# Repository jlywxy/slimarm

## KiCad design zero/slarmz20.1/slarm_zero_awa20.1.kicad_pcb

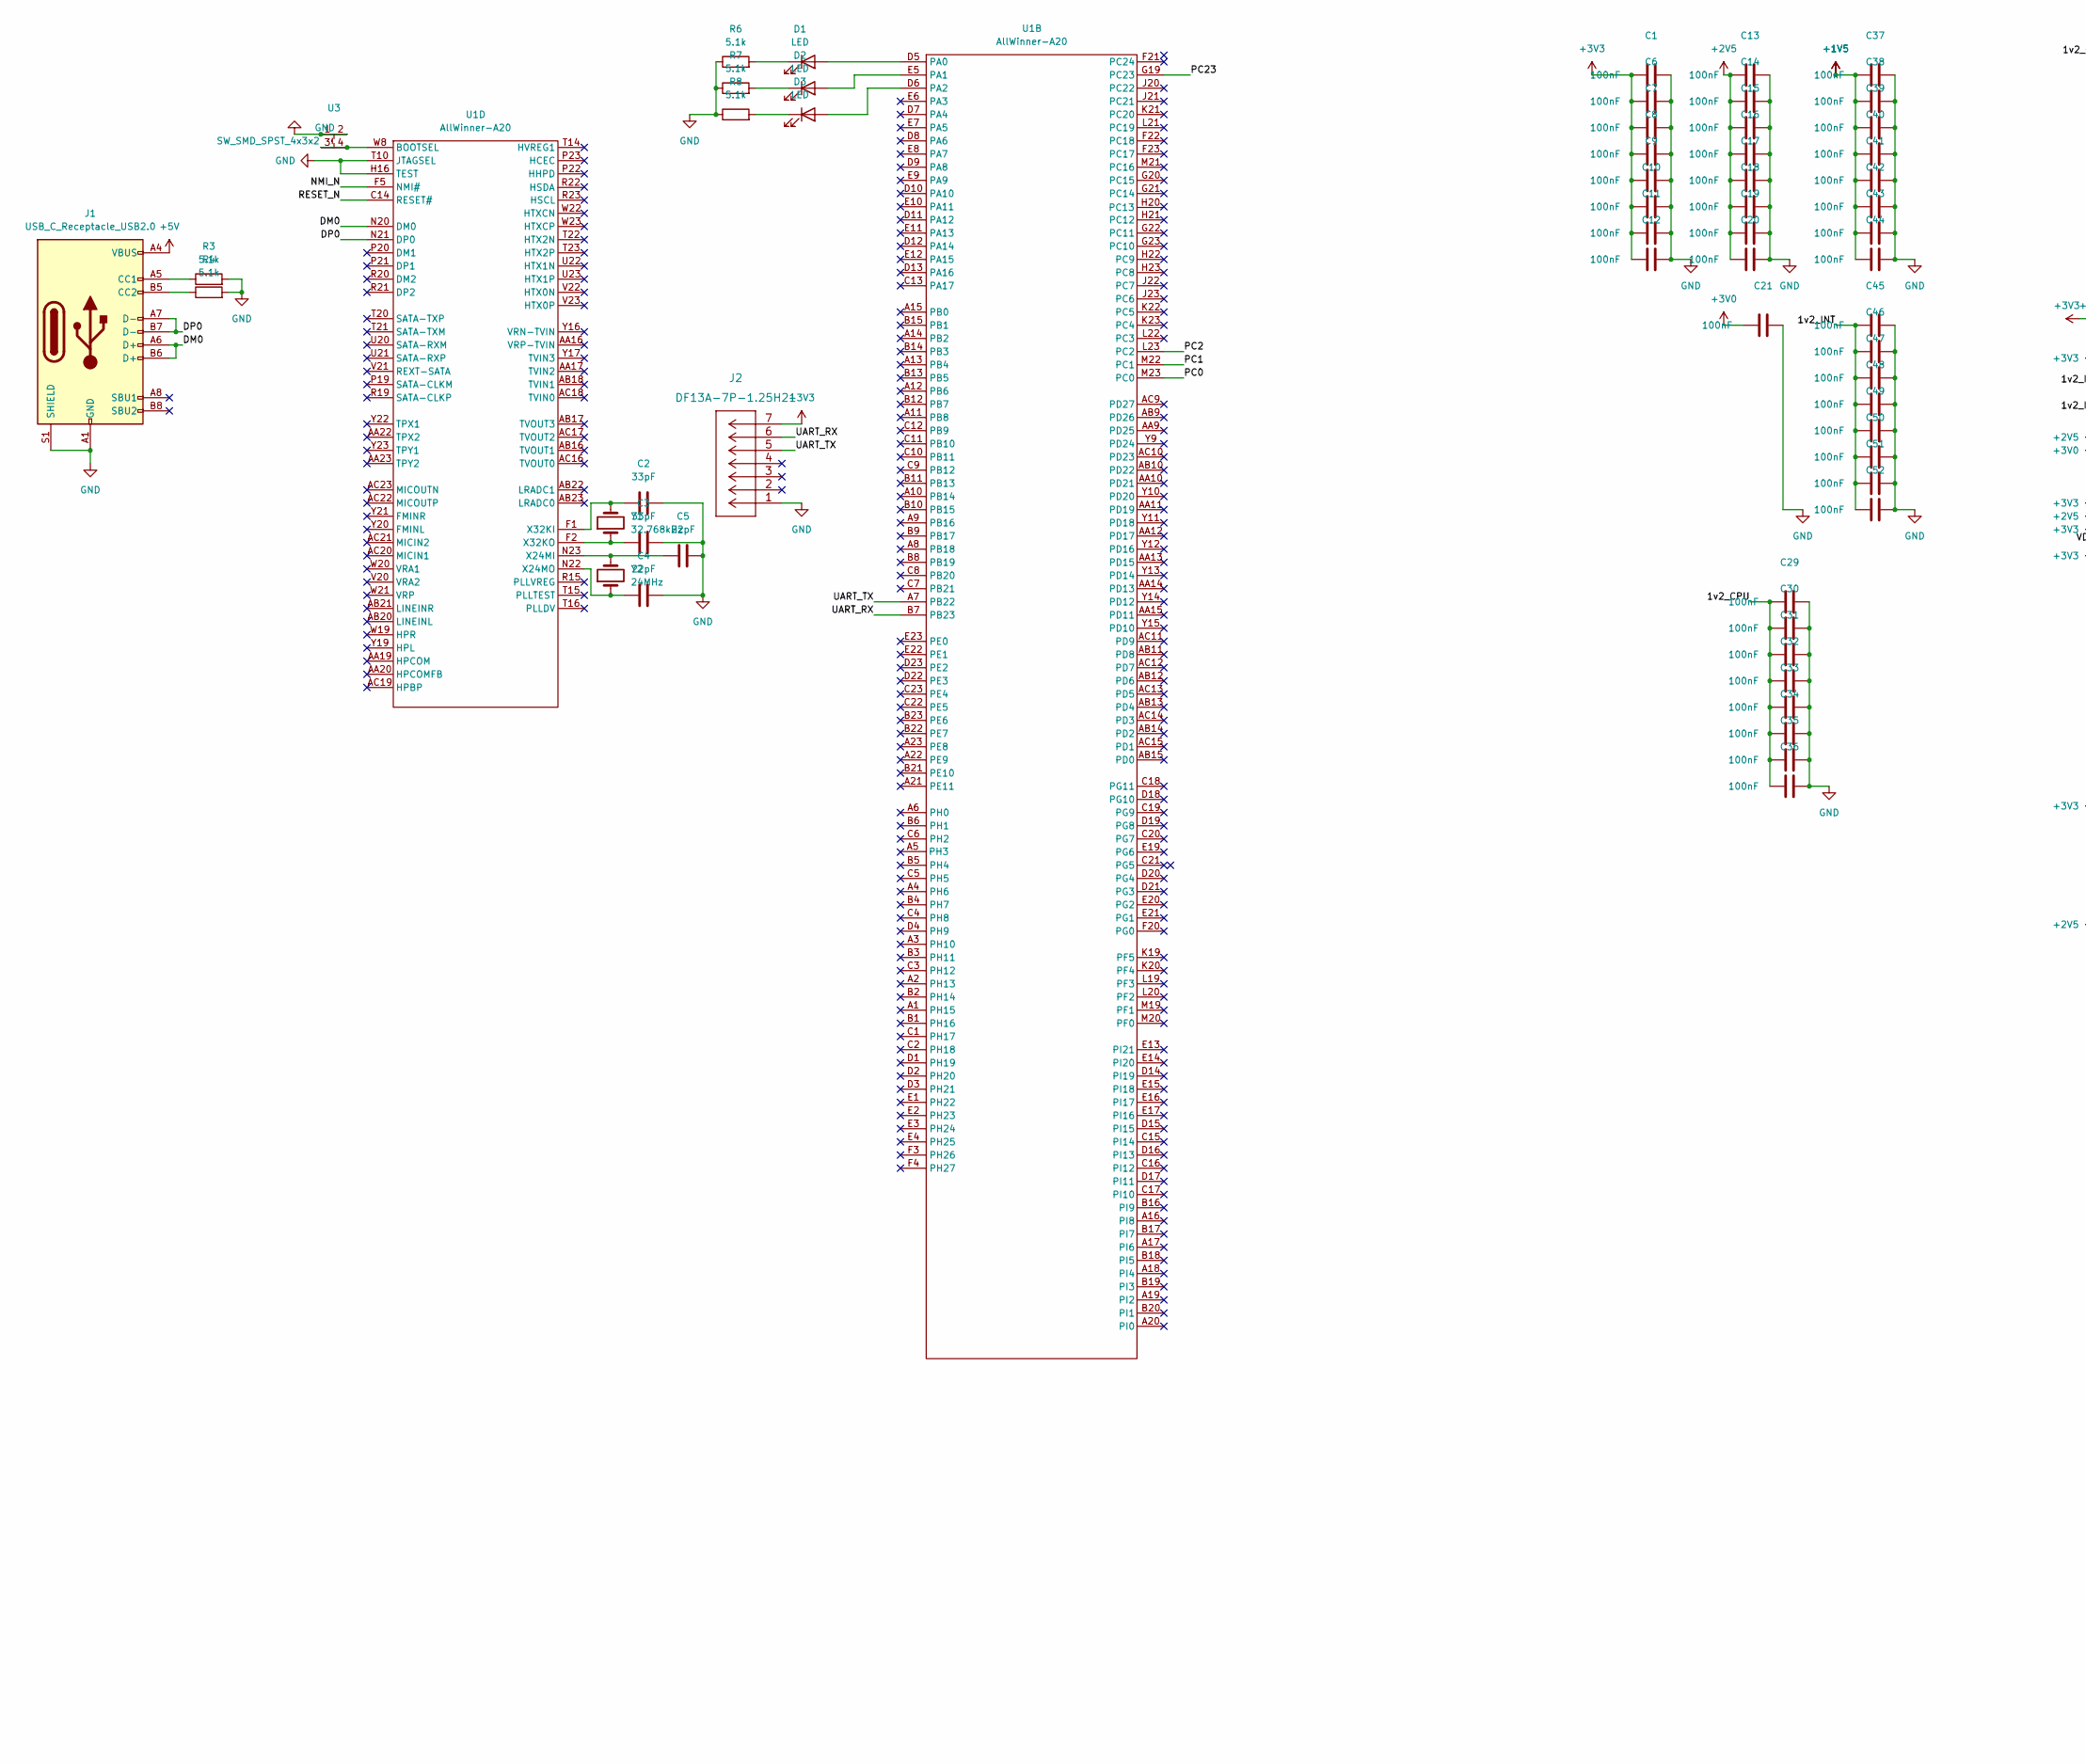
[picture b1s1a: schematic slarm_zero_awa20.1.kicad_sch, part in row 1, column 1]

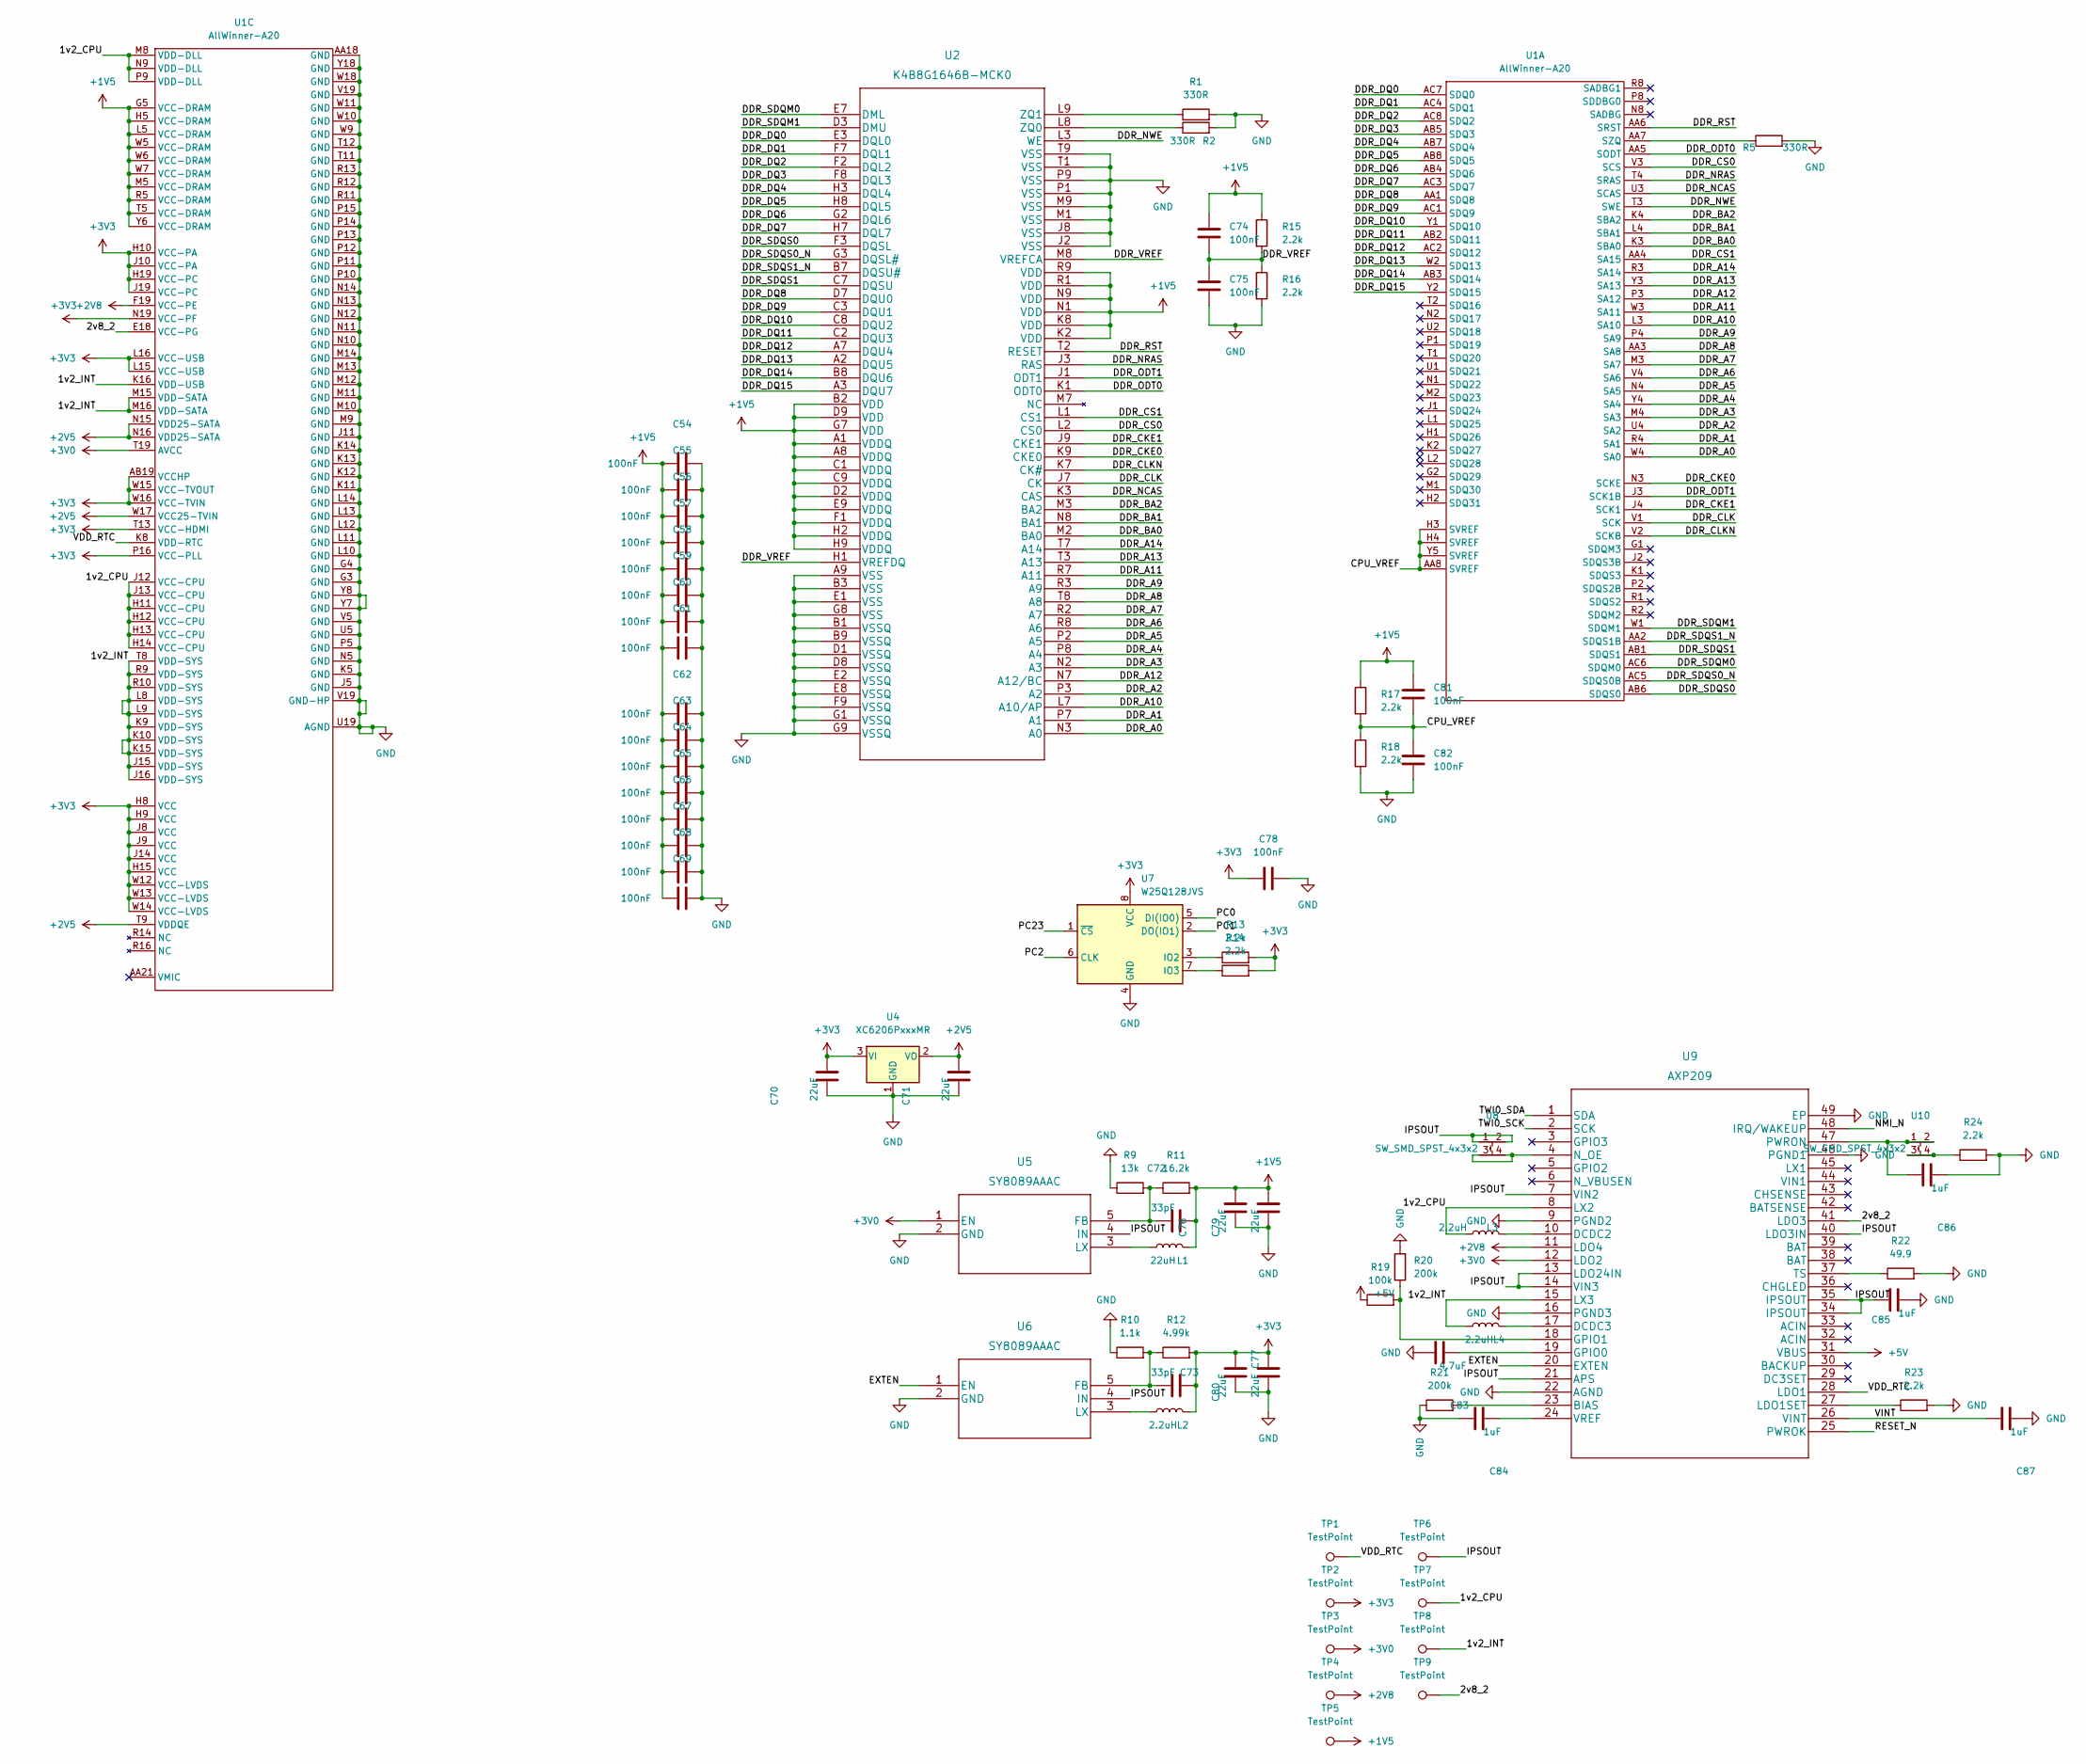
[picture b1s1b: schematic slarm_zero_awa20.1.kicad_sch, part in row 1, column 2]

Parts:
C1, C6, C7, C8, C9, C10, C11, C12, C13, C14, C15, C16, C17, C18, C19, C20, C21, C29, C30, C31, C32, C33, C34, C35, C36, C37, C38, C39, C40, C41, C42, C43, C44, C45, C46, C47, C48, C49, C50, C51, C52, C54, C55, C56, C57, C58, C59, C60, C61, C62, C63, C64, C65, C66, C67, C68, C69, C74, C75, C78, C81, C82: 100nF; C_0402_1005Metric
C2, C3: 33pF; C_0603_1608Metric
C4, C5: 22pF; C_0603_1608Metric
C70, C71, C76, C77, C79, C80: 22uF; C_0402_1005Metric
C72, C73: 33pF; C_0402_1005Metric
C83: 4.7uF; C_0402_1005Metric
C84, C85, C86, C87: 1uF; C_0402_1005Metric
D1, D2, D3: LED; LED_0603_1608Metric
J1: USB_C_Receptacle_USB2.0; USB_C_Receptacle_HRO_TYPE-C-31-M-12
J2: DF13A-7P-1.25H21
L1: 22uH; L_Vishay_IHLP-2525
L2, L3, L4: 2.2uH; L_Vishay_IHLP-2525
R1, R2, R5: 330R; R_0603_1608Metric
R3, R4, R6, R7, R8: 5.1k; R_0603_1608Metric
R9: 13k; R_0603_1608Metric
R10: 1.1k; R_0603_1608Metric
R11: 16.2k; R_0603_1608Metric
R12: 4.99k; R_0603_1608Metric
R13, R14, R15, R16, R17, R18, R23, R24: 2.2k; R_0603_1608Metric
R19: 100k; R_0603_1608Metric
R20, R21: 200k; R_0603_1608Metric
R22: 49.9; R_0603_1608Metric
TP1, TP2, TP3, TP4, TP5, TP6, TP7, TP8, TP9: TestPoint; TestPoint_Pad_D1.5mm
U1: AllWinner-A20; awa20
U2: K4B8G1646B-MCK0
U3, U8, U10: SW_SMD_SPST_4x3x2; SW_SPST_SWD_4x3x2
U4: XC6206PxxxMR; SOT-23-3
U5, U6: SY8089AAAC
U7: W25Q128JVS; SOIC-8_5.23x5.23mm_P1.27mm
U9: AXP209
Y1: 32.768kHz; Crystal_SMD_5032-2Pin_5.0x3.2mm
Y2: 24MHz; Crystal_SMD_5032-2Pin_5.0x3.2mm

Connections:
+1V5: C37.1, C38.1, C39.1, C40.1, C41.1, C42.1, C43.1, C44.1, C54.1, C55.1, C56.1, C57.1, C58.1, C59.1, C60.1, C61.1, C62.1, C63.1, C64.1, C65.1, C66.1, C67.1, C68.1, C69.1, C72.1, C74.2, C76.1, C79.1, C81.2, L1.2, R11.2, R15.1, R17.1, TP5.1, U1.G5 (VCC-DRAM), U1.H5 (VCC-DRAM), U1.L5 (VCC-DRAM), U1.M5 (VCC-DRAM), U1.R5 (VCC-DRAM), U1.T5 (VCC-DRAM), U1.W5 (VCC-DRAM), U1.W6 (VCC-DRAM), U1.W7 (VCC-DRAM), U1.Y6 (VCC-DRAM), U2.A1 (VDDQ), U2.A8 (VDDQ), U2.B2 (VDD), U2.C1 (VDDQ), U2.C9 (VDDQ), U2.D2 (VDDQ), U2.D9 (VDD), U2.E9 (VDDQ), U2.F1 (VDDQ), U2.G7 (VDD), U2.H2 (VDDQ), U2.H9 (VDDQ), U2.K2 (VDD), U2.K8 (VDD), U2.N1 (VDD), U2.N9 (VDD), U2.R1 (VDD), U2.R9 (VDD)
+2V5: C13.1, C14.1, C15.1, C16.1, C17.1, C18.1, C19.1, C20.1, C71.1, U1.N15 (VDD25-SATA), U1.N16 (VDD25-SATA), U1.T9 (VDDQE), U1.W17 (VCC25-TVIN), U4.2 (VO)
+2V8: TP4.1, U1.F19 (VCC-PE), U9.11 (LDO4)
+3V0: C21.1, TP3.1, U1.T19 (AVCC), U5.1 (EN), U9.12 (LDO2)
+3V3: C1.1, C6.1, C7.1, C8.1, C9.1, C10.1, C11.1, C12.1, C70.1, C73.1, C77.1, C78.1, C80.1, J2.7, L2.2, R12.2, R13.2, R14.2, TP2.1, U1.AB19 (VCCHP), U1.H8 (VCC), U1.H9 (VCC), U1.H10 (VCC-PA), U1.H15 (VCC), U1.H19 (VCC-PC), U1.J8 (VCC), U1.J9 (VCC), U1.J10 (VCC-PA), U1.J14 (VCC), U1.J19 (VCC-PC), U1.L15 (VCC-USB), U1.L16 (VCC-USB), U1.N19 (VCC-PF), U1.P16 (VCC-PLL), U1.T13 (VCC-HDMI), U1.W12 (VCC-LVDS), U1.W13 (VCC-LVDS), U1.W14 (VCC-LVDS), U1.W15 (VCC-TVOUT), U1.W16 (VCC-TVIN), U4.3 (VI), U7.8 (VCC)
+5V: J1.A4 (VBUS), J1.A9 (VBUS), J1.B4 (VBUS), J1.B9 (VBUS), R19.1, U9.31 (VBUS)
/1v2_CPU: C29.1, C30.1, C31.1, C32.1, C33.1, C34.1, C35.1, C36.1, L3.1, TP7.1, U1.H11 (VCC-CPU), U1.H12 (VCC-CPU), U1.H13 (VCC-CPU), U1.H14 (VCC-CPU), U1.J12 (VCC-CPU), U1.J13 (VCC-CPU), U1.M8 (VDD-DLL), U1.N9 (VDD-DLL), U1.P9 (VDD-DLL), U9.8 (LX2)
/1v2_INT: C45.1, C46.1, C47.1, C48.1, C49.1, C50.1, C51.1, C52.1, L4.1, TP8.1, U1.J15 (VDD-SYS), U1.J16 (VDD-SYS), U1.K9 (VDD-SYS), U1.K10 (VDD-SYS), U1.K15 (VDD-SYS), U1.K16 (VDD-USB), U1.L8 (VDD-SYS), U1.M15 (VDD-SATA), U1.M16 (VDD-SATA), U1.R9 (VDD-SYS), U1.R10 (VDD-SYS), U1.T8 (VDD-SYS), U9.15 (LX3)
/2v8_2: TP9.1, U1.E18 (VCC-PG), U9.41 (LDO3)
/CPU_VREF: C81.1, C82.2, R17.2, R18.1, U1.AA8 (SVREF), U1.H3 (SVREF), U1.H4 (SVREF), U1.Y5 (SVREF)
/DDR_A0: U1.W4 (SA0), U2.N3 (A0)
/DDR_A1: U1.R4 (SA1), U2.P7 (A1)
/DDR_A2: U1.U4 (SA2), U2.P3 (A2)
/DDR_A3: U1.M4 (SA3), U2.N2 (A3)
/DDR_A4: U1.Y4 (SA4), U2.P8 (A4)
/DDR_A5: U1.N4 (SA5), U2.P2 (A5)
/DDR_A6: U1.V4 (SA6), U2.R8 (A6)
/DDR_A7: U1.M3 (SA7), U2.R2 (A7)
/DDR_A8: U1.AA3 (SA8), U2.T8 (A8)
/DDR_A9: U1.P4 (SA9), U2.R3 (A9)
/DDR_A10: U1.L3 (SA10), U2.L7 (A10/AP)
/DDR_A11: U1.W3 (SA11), U2.R7 (A11)
/DDR_A12: U1.P3 (SA12), U2.N7 (A12/BC)
/DDR_A13: U1.Y3 (SA13), U2.T3 (A13)
/DDR_A14: U1.R3 (SA14), U2.T7 (A14)
/DDR_BA0: U1.K3 (SBA0), U2.M2 (BA0)
/DDR_BA1: U1.L4 (SBA1), U2.N8 (BA1)
/DDR_BA2: U1.K4 (SBA2), U2.M3 (BA2)
/DDR_CKE0: U1.N3 (SCKE), U2.K9 (CKE0)
/DDR_CKE1: U1.J4 (SCK1), U2.J9 (CKE1)
/DDR_CLK: U1.V1 (SCK), U2.J7 (CK)
/DDR_CLKN: U1.V2 (SCKB), U2.K7 (CK#)
/DDR_CS0: U1.V3 (SCS), U2.L2 (CS0)
/DDR_CS1: U1.AA4 (SA15), U2.L1 (CS1)
/DDR_DQ0: U1.AC7 (SDQ0), U2.E3 (DQL0)
/DDR_DQ1: U1.AC4 (SDQ1), U2.F7 (DQL1)
/DDR_DQ2: U1.AC8 (SDQ2), U2.F2 (DQL2)
/DDR_DQ3: U1.AB5 (SDQ3), U2.F8 (DQL3)
/DDR_DQ4: U1.AB7 (SDQ4), U2.H3 (DQL4)
/DDR_DQ5: U1.AB8 (SDQ5), U2.H8 (DQL5)
/DDR_DQ6: U1.AB4 (SDQ6), U2.G2 (DQL6)
/DDR_DQ7: U1.AC3 (SDQ7), U2.H7 (DQL7)
/DDR_DQ8: U1.AA1 (SDQ8), U2.D7 (DQU0)
/DDR_DQ9: U1.AC1 (SDQ9), U2.C3 (DQU1)
/DDR_DQ10: U1.Y1 (SDQ10), U2.C8 (DQU2)
/DDR_DQ11: U1.AB2 (SDQ11), U2.C2 (DQU3)
/DDR_DQ12: U1.AC2 (SDQ12), U2.A7 (DQU4)
/DDR_DQ13: U1.W2 (SDQ13), U2.A2 (DQU5)
/DDR_DQ14: U1.AB3 (SDQ14), U2.B8 (DQU6)
/DDR_DQ15: U1.Y2 (SDQ15), U2.A3 (DQU7)
/DDR_NCAS: U1.U3 (SCAS), U2.K3 (CAS)
/DDR_NRAS: U1.T4 (SRAS), U2.J3 (RAS)
/DDR_NWE: U1.T3 (SWE), U2.L3 (WE)
/DDR_ODT0: U1.AA5 (SODT), U2.K1 (ODT0)
/DDR_ODT1: U1.J3 (SCK1B), U2.J1 (ODT1)
/DDR_RST: U1.AA6 (SRST), U2.T2 (RESET)
/DDR_SDQM0: U1.AC6 (SDQM0), U2.E7 (DML)
/DDR_SDQM1: U1.W1 (SDQM1), U2.D3 (DMU)
/DDR_SDQS0: U1.AB6 (SDQS0), U2.F3 (DQSL)
/DDR_SDQS0_N: U1.AC5 (SDQS0B), U2.G3 (DQSL#)
/DDR_SDQS1: U1.AB1 (SDQS1), U2.C7 (DQSU)
/DDR_SDQS1_N: U1.AA2 (SDQS1B), U2.B7 (DQSU#)
/DDR_VREF: C74.1, C75.2, R15.2, R16.1, U2.H1 (VREFDQ), U2.M8 (VREFCA)
/DM0: J1.A6 (D+), J1.B6 (D+), U1.N20 (DM0)
/DP0: J1.A7 (D-), J1.B7 (D-), U1.N21 (DP0)
/EXTEN: U6.1 (EN), U9.20 (EXTEN)
/IPSOUT: C85.1, TP6.1, U5.4 (IN), U6.4 (IN), U8.1, U8.2, U9.7 (VIN2), U9.13 (LDO24IN), U9.14 (VIN3), U9.21 (APS), U9.34 (IPSOUT), U9.35 (IPSOUT), U9.40 (LDO3IN)
/NMI_N: U1.F5 (NMI#), U9.48 (IRQ/WAKEUP)
/PC0: U1.M23 (PC0), U7.5 (DI(IO0))
/PC1: U1.M22 (PC1), U7.2 (DO(IO1))
/PC2: U1.L23 (PC2), U7.6 (CLK)
/PC23: U1.G19 (PC23), U7.1 (~CS)
/RESET_N: U1.C14 (RESET#), U9.25 (PWROK)
/TWI0_SCK: U9.2 (SCK)
/TWI0_SDA: U9.1 (SDA)
/UART_RX: J2.6, U1.B7 (PB23)
/UART_TX: J2.5, U1.A7 (PB22)
/VDD_RTC: TP1.1, U1.K8 (VDD-RTC), U9.28 (LDO1)
/VINT: C87.1, U9.26 (VINT)
GND: C1.2, C2.2, C3.2, C4.2, C5.2, C6.2, C7.2, C8.2, C9.2, C10.2, C11.2, C12.2, C13.2, C14.2, C15.2, C16.2, C17.2, C18.2, C19.2, C20.2, C21.2, C29.2, C30.2, C31.2, C32.2, C33.2, C34.2, C35.2, C36.2, C37.2, C38.2, C39.2, C40.2, C41.2, C42.2, C43.2, C44.2, C45.2, C46.2, C47.2, C48.2, C49.2, C50.2, C51.2, C52.2, C54.2, C55.2, C56.2, C57.2, C58.2, C59.2, C60.2, C61.2, C62.2, C63.2, C64.2, C65.2, C66.2, C67.2, C68.2, C69.2, C70.2, C71.2, C75.1, C76.2, C77.2, C78.2, C79.2, C80.2, C82.1, C83.1, C84.1, C85.2, C86.2, C87.2, J1.A1 (GND), J1.A12 (GND), J1.B1 (GND), J1.B12 (GND), J1.S1 (SHIELD), J2.1, R1.2, R2.2, R3.2, R4.2, R5.2, R6.1, R7.1, R8.1, R9.1, R10.1, R16.2, R18.2, R20.2, R21.1, R22.2, R23.2, R24.2, U1.AA18 (GND), U1.G3 (GND), U1.G4 (GND), U1.H16 (TEST), U1.J5 (GND), U1.J11 (GND), U1.K5 (GND), U1.K11 (GND), U1.K12 (GND), U1.K13 (GND), U1.K14 (GND), U1.L10 (GND), U1.L11 (GND), U1.L12 (GND), U1.L13 (GND), U1.L14 (GND), U1.M9 (GND), U1.M10 (GND), U1.M11 (GND), U1.M12 (GND), U1.M13 (GND), U1.M14 (GND), U1.N5 (GND), U1.N10 (GND), U1.N11 (GND), U1.N12 (GND), U1.N13 (GND), U1.N14 (GND), U1.P5 (GND), U1.P10 (GND), U1.P11 (GND), U1.P12 (GND), U1.P13 (GND), U1.P14 (GND), U1.P15 (GND), U1.R11 (GND), U1.R12 (GND), U1.R13 (GND), U1.T10 (JTAGSEL), U1.T11 (GND), U1.T12 (GND), U1.U5 (GND), U1.V5 (GND), U1.V19 (GND), U1.W9 (GND), U1.W10 (GND), U1.W11 (GND), U1.W18 (GND), U1.Y7 (GND), U1.Y8 (GND), U1.Y18 (GND), U2.A9 (VSS), U2.B1 (VSSQ), U2.B3 (VSS), U2.B9 (VSSQ), U2.D1 (VSSQ), U2.D8 (VSSQ), U2.E1 (VSS), U2.E2 (VSSQ), U2.E8 (VSSQ), U2.F9 (VSSQ), U2.G1 (VSSQ), U2.G8 (VSS), U2.G9 (VSSQ), U2.J2 (VSS), U2.J8 (VSS), U2.M1 (VSS), U2.M9 (VSS), U2.P1 (VSS), U2.P9 (VSS), U2.T1 (VSS), U2.T9 (VSS), U3.1, U3.2, U4.1 (GND), U5.2 (GND), U6.2 (GND), U7.4 (GND), U9.9 (PGND2), U9.16 (PGND3), U9.22 (AGND), U9.46 (PGND1), U9.49 (EP)
unnamed: C72.2, R9.2, R11.1, U5.5 (FB)
unnamed: C73.2, R10.2, R12.1, U6.5 (FB)
unnamed: C83.2, U9.19 (GPIO0)
unnamed: C84.2, U9.24 (VREF)
unnamed: C86.1, U9.47 (PWRON), U10.1, U10.2
unnamed: D1.1 (K), R6.2
unnamed: D2.1 (K), R7.2
unnamed: D3.1 (K), R8.2
unnamed: J1.A5 (CC1), R3.1
unnamed: J1.B5 (CC2), R4.1
unnamed: L1.1, U5.3 (LX)
unnamed: L2.1, U6.3 (LX)
unnamed: L3.2, U9.10 (DCDC2)
unnamed: L4.2, U9.17 (DCDC3)
unnamed: R1.1, U2.L9 (ZQ1)
unnamed: R2.1, U2.L8 (ZQ0)
unnamed: R5.1, U1.AA7 (SZQ)
unnamed: R13.1, U7.3 (IO2)
unnamed: R14.1, U7.7 (IO3)
unnamed: R19.2, R20.1, U9.18 (GPIO1)
unnamed: R21.2, U9.23 (BIAS)
unnamed: R22.1, U9.37 (TS)
unnamed: R23.1, U9.27 (LDO1SET)
unnamed: R24.1, U10.3, U10.4
unnamed: D1.2 (A), U1.D5 (PA0)
unnamed: D3.2 (A), U1.D6 (PA2)
unnamed: D2.2 (A), U1.E5 (PA1)
unnamed: C2.1, U1.F1 (X32KI), Y1.2
unnamed: C3.1, U1.F2 (X32KO), Y1.1
unnamed: C4.1, U1.N22 (X24MO), Y2.1
unnamed: C5.1, U1.N23 (X24MI), Y2.2
unnamed: U1.W8 (BOOTSEL), U3.3, U3.4
unnamed: U8.3, U8.4, U9.4 (N_OE)

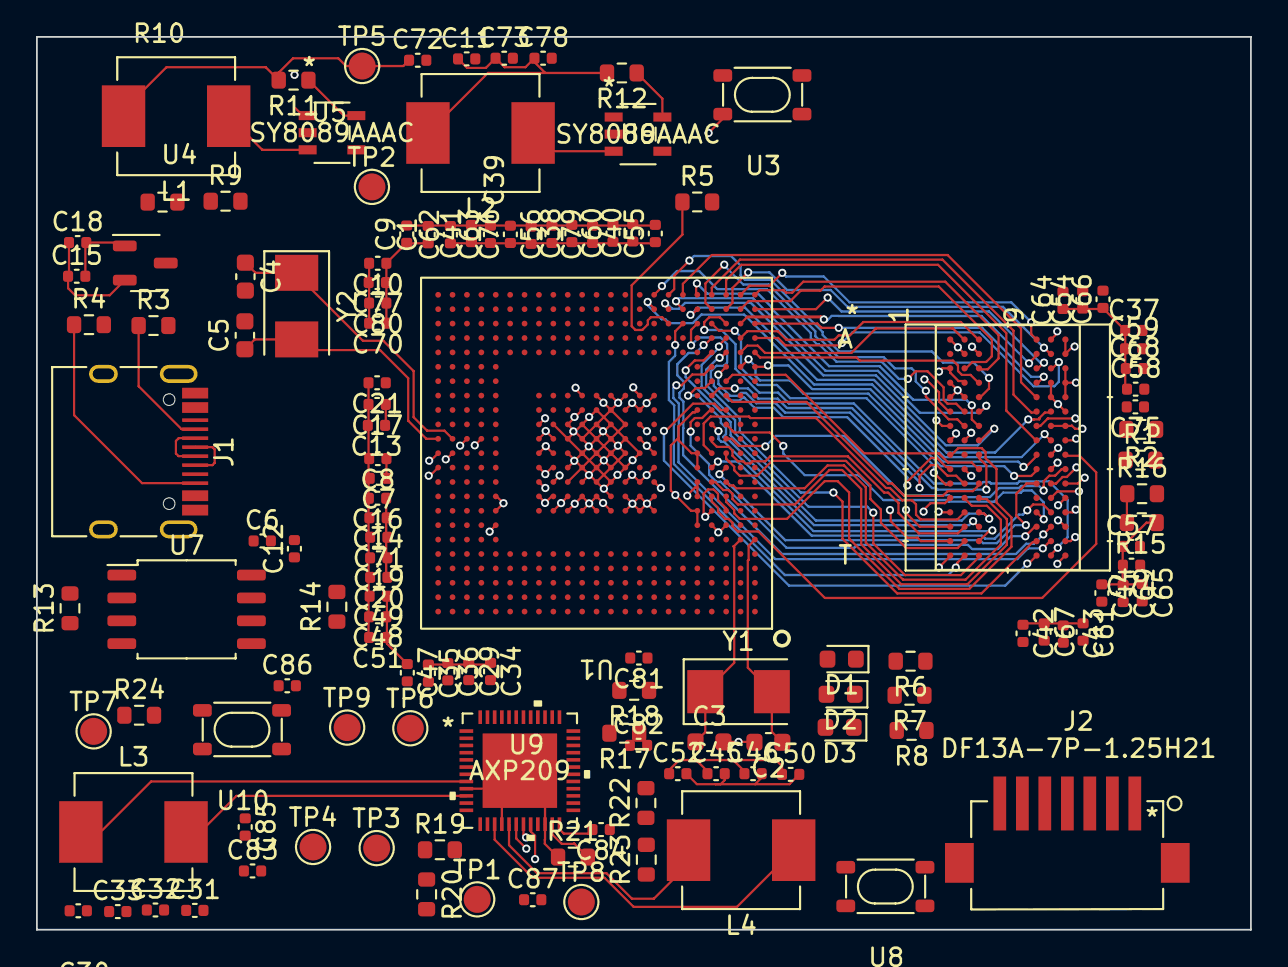
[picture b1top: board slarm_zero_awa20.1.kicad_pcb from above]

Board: 4 copper layers, 67.4 x 49.6 mm, 133 parts (0 on the bottom side), 111 nets.

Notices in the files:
parts and their libraries:
Copyright 2021 Accelerated Designs. All rights reserved.
